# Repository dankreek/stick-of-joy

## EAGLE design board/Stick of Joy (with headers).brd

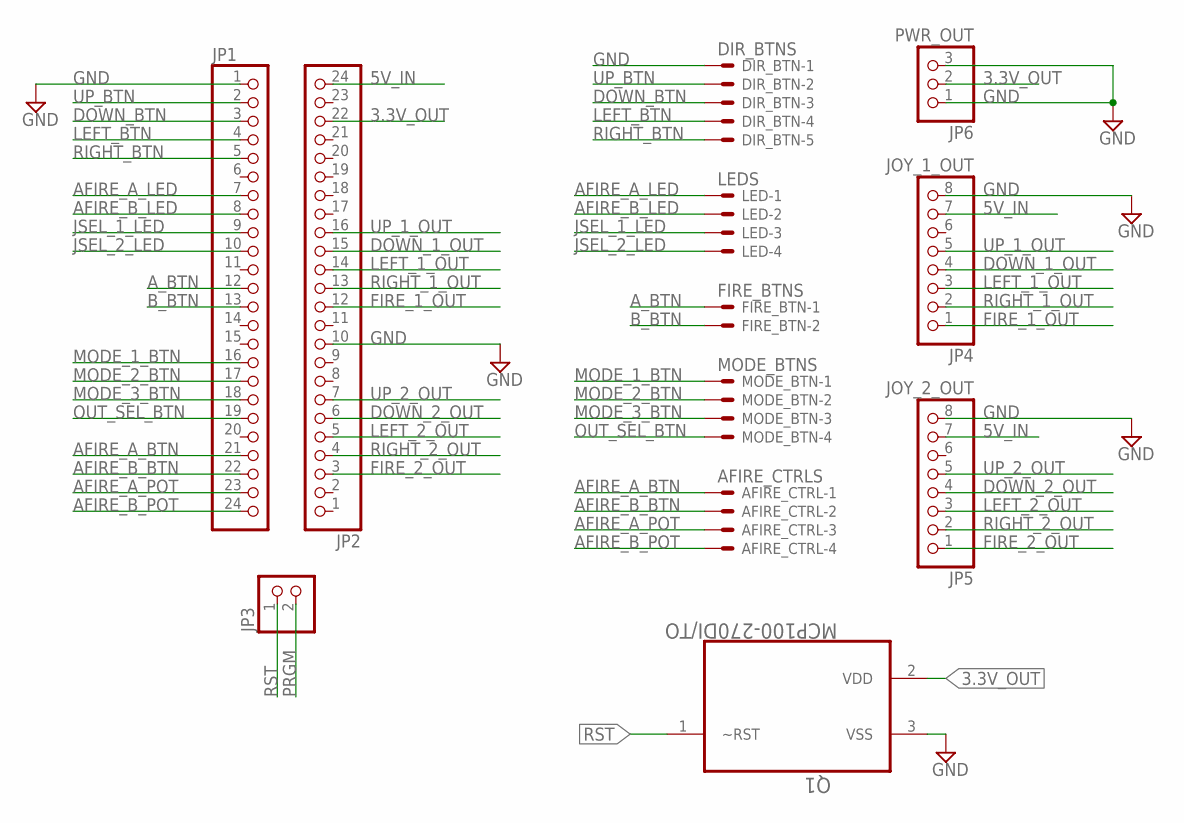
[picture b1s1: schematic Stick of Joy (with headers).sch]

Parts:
AFIRE_CTRL: AFIRE_CTRLS; JST-XH-04-PACKAGE-ROUND-PAD
DIR_BTN: DIR_BTNS; JST-XH-05-PACKAGE-ROUND-PAD
FIRE_BTN: FIRE_BTNS; JST-XH-02-PACKAGE-ROUND-PAD
JP1, JP2: PINHD-1X24; 1X24
JP3: PINHD-1X2; 1X02
JP4: JOY_1_OUT; 1X08
JP5: JOY_2_OUT; 1X08
JP6: PWR_OUT; 1X03
LED: LEDS; JST-XH-04-PACKAGE-ROUND-PAD
MODE_BTN: MODE_BTNS; JST-XH-04-PACKAGE-ROUND-PAD
Q1: MCP100-270DI/TO; TO127P254X495-3

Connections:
3.3V_OUT: JP2.22, JP6.2, Q1.2 (VDD)
5V_IN: JP2.24, JP4.7, JP5.7
AFIRE_A_BTN: AFIRE_CTRL.1, JP1.21
AFIRE_A_LED: JP1.7, LED.1
AFIRE_A_POT: AFIRE_CTRL.3, JP1.23
AFIRE_B_BTN: AFIRE_CTRL.2, JP1.22
AFIRE_B_LED: JP1.8, LED.2
AFIRE_B_POT: AFIRE_CTRL.4, JP1.24
A_BTN: FIRE_BTN.1, JP1.12
B_BTN: FIRE_BTN.2, JP1.13
DOWN_1_OUT: JP2.15, JP4.4
DOWN_2_OUT: JP2.6, JP5.4
DOWN_BTN: DIR_BTN.3, JP1.3
FIRE_1_OUT: JP2.12, JP4.1
FIRE_2_OUT: JP2.3, JP5.1
GND: DIR_BTN.1, JP1.1, JP2.10, JP4.8, JP5.8, JP6.1, JP6.3, Q1.3 (VSS)
JSEL_1_LED: JP1.9, LED.3
JSEL_2_LED: JP1.10, LED.4
LEFT_1_OUT: JP2.14, JP4.3
LEFT_2_OUT: JP2.5, JP5.3
LEFT_BTN: DIR_BTN.4, JP1.4
MODE_1_BTN: JP1.16, MODE_BTN.1
MODE_2_BTN: JP1.17, MODE_BTN.2
MODE_3_BTN: JP1.18, MODE_BTN.3
OUT_SEL_BTN: JP1.19, MODE_BTN.4
PRGM: JP3.2
RIGHT_1_OUT: JP2.13, JP4.2
RIGHT_2_OUT: JP2.4, JP5.2
RIGHT_BTN: DIR_BTN.5, JP1.5
RST: JP3.1, Q1.1 (~RST)
UP_1_OUT: JP2.16, JP4.5
UP_2_OUT: JP2.7, JP5.5
UP_BTN: DIR_BTN.2, JP1.2

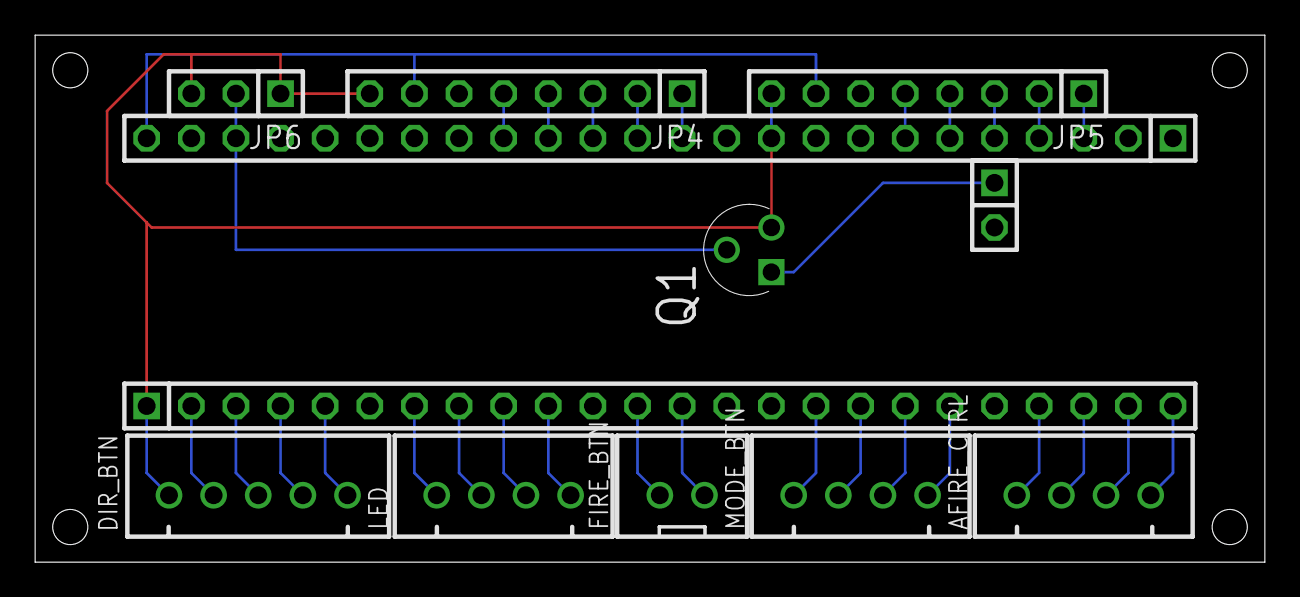
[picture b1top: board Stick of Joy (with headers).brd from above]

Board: 2 copper layers, 70.0 x 30.0 mm, 12 parts (0 on the bottom side), 32 nets.

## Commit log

2018-04-29 [1] Add hardware libs
2018-04-29 [2] Add input modules
2018-05-01 [4] Add input modes
2018-05-01 [3] Create the input router
2018-05-01 [5] Tie together all components
2018-05-01 [6] Create logger
2018-05-01 [3] Add logging to InputRouter
2018-05-01 [4] Add logging to PlatformGameMode
2018-05-01 [1] Update inputs
2018-05-01 Add logging to JoystickOut
2018-05-01 Make joystick out state public readible
2018-05-01 Log route on single line
2018-05-02 Key joystick in state for changing modes and outs
2018-05-03 Add joy port switching indication and state transfer
2018-05-07 Hook up autofire LEDs
2018-05-07 Turn off built-in LED after setup()
2018-05-07 [8] Reverse A and B buttons in PlatformGameMode
    Resolves #8
2018-05-08 [9] Make Pot interface similar to IInputButton
    Resolves #9
2018-05-13 [10] Add single button mode
    Resolves #10
2018-05-16 [11] a-as-space dual-stick mode added
    Resolves #11
2018-05-16 need to clean up analog in
2018-05-17 Reduce speed to 24Mhz to reduce power consumption
2018-06-05 [14] Rearrange inputs for new design
    Resolves #14
2018-06-15 Update setting for new PIO version
2018-06-15 Remove logging of a. fire pots for now
2018-06-15 [15] Find min comfortable LED brightness and refactor
2018-06-15 [15] Find min comfortable LED brightness and refactor
    Resolves #15
2018-06-19 [12] Add LED brightness transitions
    Resolves #12
2018-06-19 Reading pots at correct resolution
2018-06-22 Adjust PWM LED resolution and fade speeds
2018-06-24 [7] Add auto-fire functionality
    Resolves #7
2018-10-15 Add eagle schematic and board design
2018-10-15 Say, "HO!" if you ever had a J-O
2018-10-16 Lower LED brightness to conserve power
2018-10-21 [13] Refactor to send pointer to new modes from mode selector
